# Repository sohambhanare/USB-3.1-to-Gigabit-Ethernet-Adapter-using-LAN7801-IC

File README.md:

# USB-3.1-to-Gigabit-Ethernet-Adapter-using-LAN7801-IC
KiCad design of a USB 3.1 Gen 1 to Gigabit Ethernet adapter based on the LAN7801 and KSZ9031RNX. Includes schematic, 4-layer impedance-controlled PCB layout, power supply design, simulations, and manufacturing Gerbers.

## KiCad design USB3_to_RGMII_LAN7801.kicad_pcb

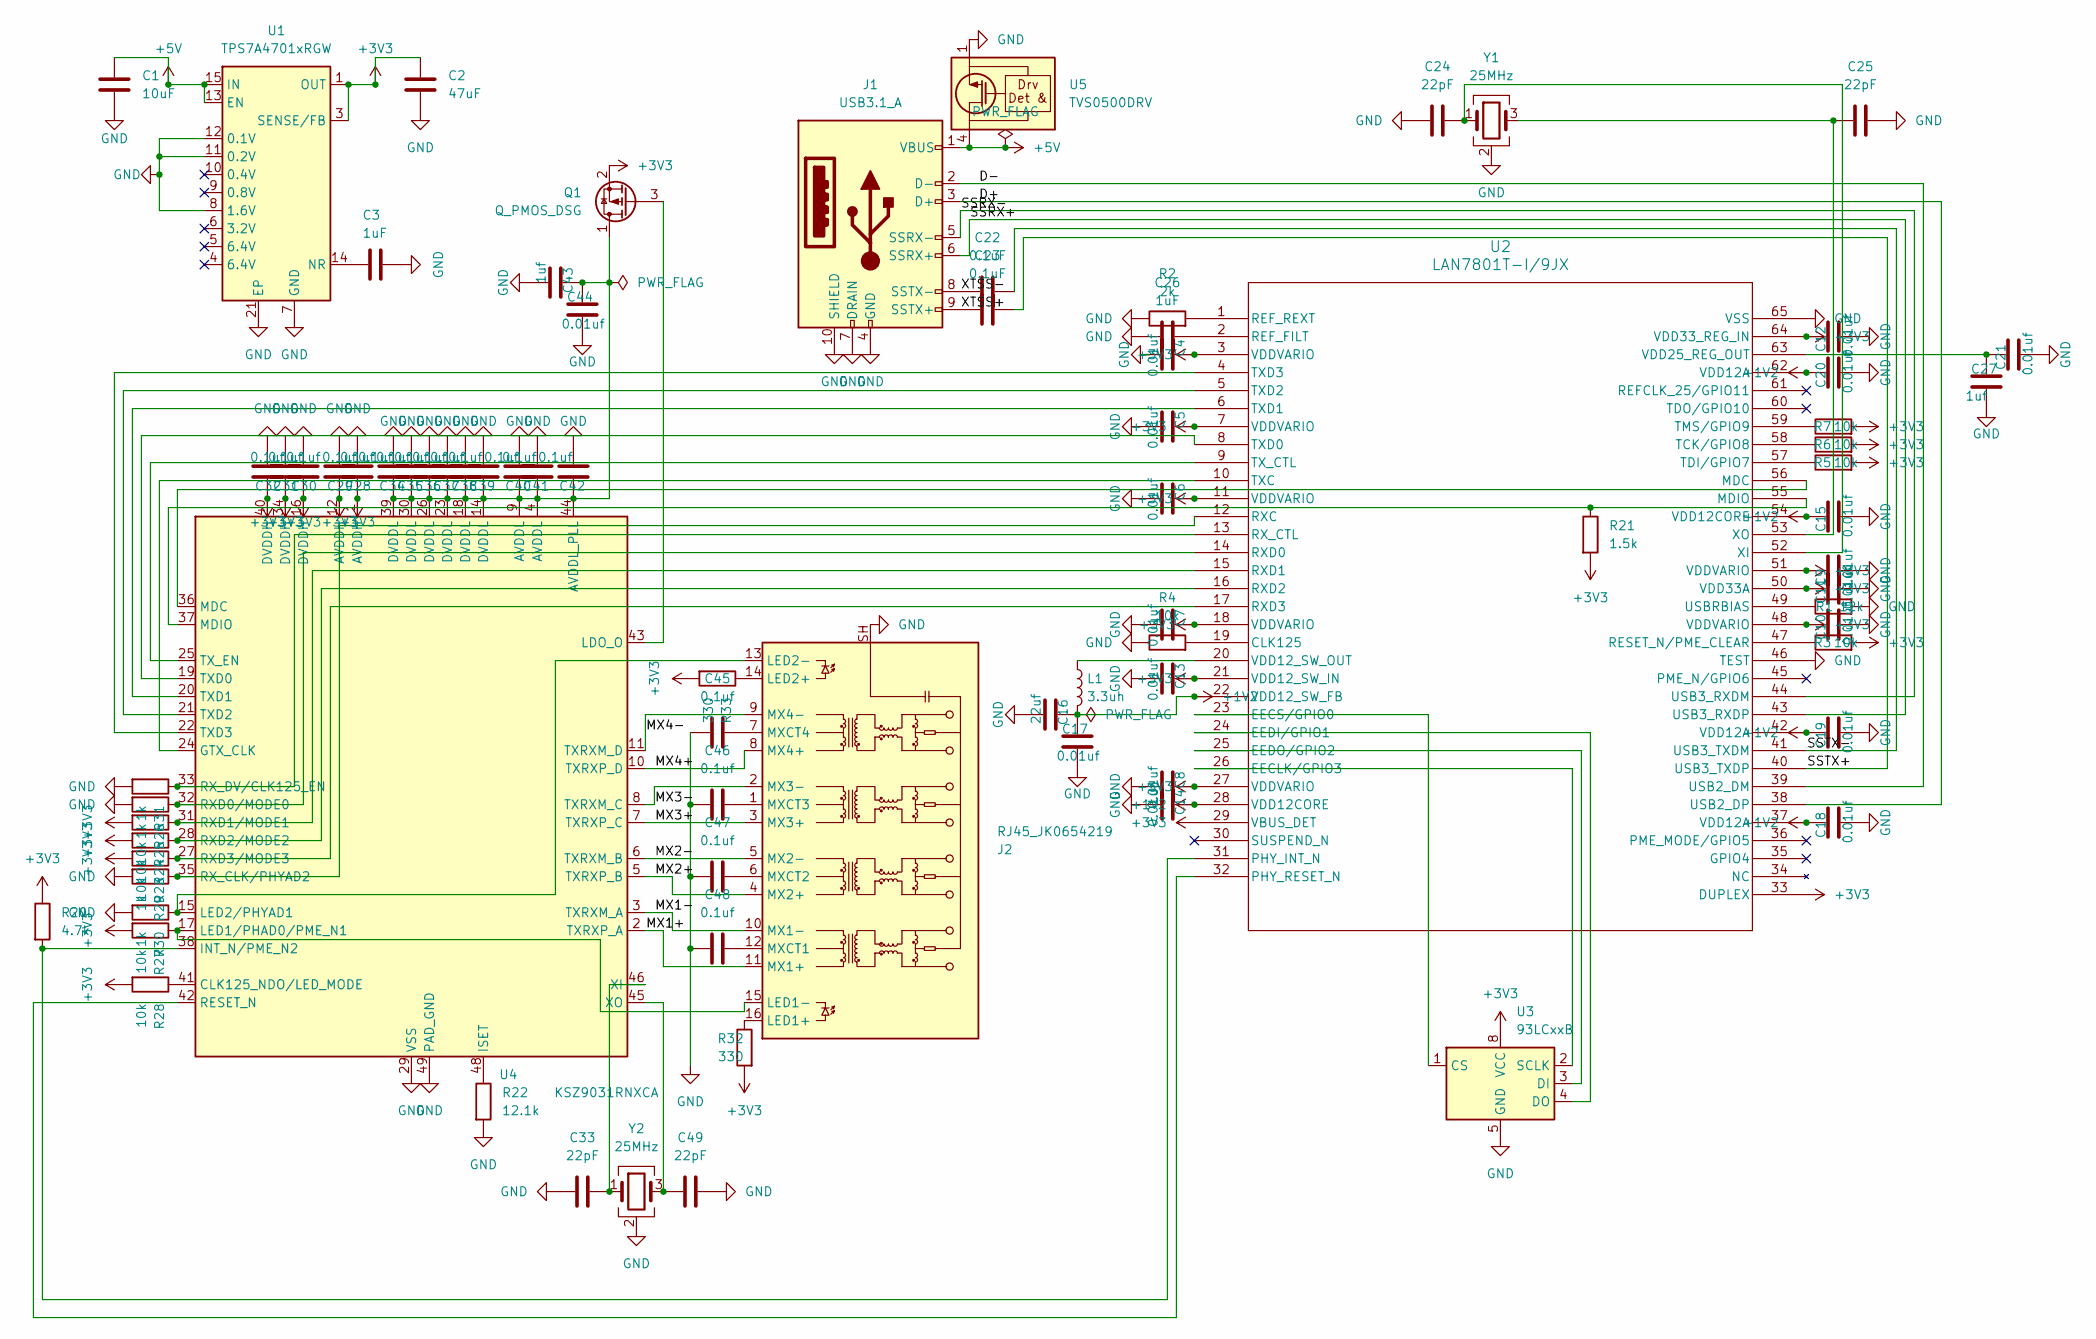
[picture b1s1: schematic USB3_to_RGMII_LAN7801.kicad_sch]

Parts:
C1: 10uF; C_0603_1608Metric
C2: 47uF; C_0603_1608Metric
C3, C26: 1uF; C_0603_1608Metric
C4, C5, C6, C7, C8, C9, C10, C11, C12, C13, C14, C15, C17, C18, C19, C20, C21, C44: 0.01uf; C_0603_1608Metric
C16: 22uf; C_0603_1608Metric
C22, C23: 0.1uF; C_0603_1608Metric
C24, C25, C33, C49: 22pF; C_0603_1608Metric
C27, C43: 1uf; C_0603_1608Metric
C28, C29, C30, C31, C32, C34, C35, C36, C37, C38, C39, C40, C41, C42, C45, C46, C47, C48: 0.1uf; C_0603_1608Metric
J1: USB3.1_A; USB3_A_Molex_48393-001
J2: RJ45_JK0654219; RJ45_Pulse_JK0654219NL_Horizontal
L1: 3.3uh; L_0603_1608Metric
Q1: Q_PMOS_DSG; SOT-23
R1: 12k; R_0603_1608Metric
R2: 2k; R_0603_1608Metric
R3, R4, R5, R6, R7, R23, R24, R25, R27, R28: 10k; R_0603_1608Metric
R20: 4.7k; R_0603_1608Metric
R21: 1.5k; R_0603_1608Metric
R22: 12.1k; R_0603_1608Metric
R26, R29, R30, R31: 1k; R_0603_1608Metric
R32, R33: 330; R_0603_1608Metric
U1: TPS7A4701xRGW; Texas_RGW0020A_VQFN-20-1EP_5x5mm_P0.65mm_EP3.15x3.15mm_Ther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
U2: LAN7801T-I/9JX; VQFN64_9X9X0P9_R4_MCH
U3: 93LCxxB; SOIC-8_3.9x4.9mm_P1.27mm
U4: KSZ9031RNXCA; QFN-48-1EP_7x7mm_P0.5mm_EP5.15x5.15mm
U5: TVS0500DRV; WSON-6-1EP_2x2mm_P0.65mm_EP1x1.6mm
Y1, Y2: 25MHz; Crystal_SMD_3225-4Pin_3.2x2.5mm

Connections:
+1V2: C14.1, C15.1, C16.1, C17.1, C18.1, C19.1, C20.1, L1.2, U2.22 (VDD12_SW_FB), U2.28 (VDD12CORE), U2.37 (VDD12A), U2.42 (VDD12A), U2.54 (VDD12CORE), U2.62 (VDD12A)
+3V3: C2.1, C4.1, C5.1, C6.1, C7.1, C8.1, C9.1, C10.1, C11.1, C12.1, C13.1, C28.1, C29.1, C30.1, C31.1, C32.1, Q1.2 (S), R3.2, R5.2, R6.2, R7.2, R20.1, R21.2, R23.2, R24.2, R25.2, R27.2, R28.2, R32.2, R33.2, U1.1 (OUT), U1.3 (SENSE/FB), U1.20 (OUT), U2.3 (VDDVARIO), U2.7 (VDDVARIO), U2.11 (VDDVARIO), U2.18 (VDDVARIO), U2.21 (VDD12_SW_IN), U2.27 (VDDVARIO), U2.29 (VBUS_DET), U2.33 (DUPLEX), U2.48 (VDDVARIO), U2.50 (VDD33A), U2.51 (VDDVARIO), U2.64 (VDD33_REG_IN), U3.8 (VCC), U4.1 (AVDDH), U4.12 (AVDDH), U4.16 (DVDDH), U4.34 (DVDDH), U4.40 (DVDDH)
+5V: C1.1, J1.1 (VBUS), U1.13 (EN), U1.15 (IN), U1.16 (IN), U5.4 (IN), U5.5 (IN), U5.6 (IN)
/D+: J1.3 (D+), U2.38 (USB2_DP)
/D-: J1.2 (D-), U2.39 (USB2_DM)
/MX1+: J2.11 (MX1+), U4.2 (TXRXP_A)
/MX1-: J2.10 (MX1-), U4.3 (TXRXM_A)
/MX2+: J2.4 (MX2+), U4.5 (TXRXP_B)
/MX2-: J2.5 (MX2-), U4.6 (TXRXM_B)
/MX3+: J2.3 (MX3+), U4.7 (TXRXP_C)
/MX3-: J2.2 (MX3-), U4.8 (TXRXM_C)
/MX4+: J2.8 (MX4+), U4.10 (TXRXP_D)
/MX4-: J2.9 (MX4-), U4.11 (TXRXM_D)
/SSRX+: J1.6 (SSRX+), U2.43 (USB3_RXDP)
/SSRX-: J1.5 (SSRX-), U2.44 (USB3_RXDM)
/SSTX+: C23.2, U2.40 (USB3_TXDP)
/SSTX-: C22.2, U2.41 (USB3_TXDM)
/XTSS+: C23.1, J1.9 (SSTX+)
/XTSS-: C22.1, J1.8 (SSTX-)
GND: C1.2, C2.2, C3.2, C4.2, C5.2, C6.2, C7.2, C8.2, C9.2, C10.2, C11.2, C12.2, C13.2, C14.2, C15.2, C16.2, C17.2, C18.2, C19.2, C20.2, C21.2, C24.1, C25.2, C26.1, C27.2, C28.2, C29.2, C30.2, C31.2, C32.2, C33.1, C34.2, C35.2, C36.2, C37.2, C38.2, C39.2, C40.2, C41.2, C42.2, C43.2, C44.2, C45.1, C46.1, C47.1, C48.1, C49.2, J1.4 (GND), J1.7 (DRAIN), J1.10 (SHIELD), J2.SH, R1.2, R2.1, R4.1, R22.2, R26.2, R29.2, R30.2, R31.2, U1.7 (GND), U1.8 (1.6V), U1.11 (0.2V), U1.12 (0.1V), U1.21 (EP), U2.46 (TEST), U2.65 (VSS), U3.5 (GND), U4.29 (VSS), U4.49 (PAD_GND), U5.1 (GND), U5.2 (GND), U5.3 (GND), U5.7 (GND), Y1.2 (G), Y1.4 (G), Y2.2 (G), Y2.4 (G)
unnamed: J2.16 (LED1+), R32.1
unnamed: J2.15 (LED1-), R27.1, U4.17 (LED1/PHAD0/PME_N1)
unnamed: J2.14 (LED2+), R33.1
unnamed: J2.13 (LED2-), R30.1, U4.15 (LED2/PHYAD1)
unnamed: C48.2, J2.12 (MXCT1)
unnamed: C47.2, J2.6 (MXCT2)
unnamed: C46.2, J2.1 (MXCT3)
unnamed: C45.2, J2.7 (MXCT4)
unnamed: C34.1, C35.1, C36.1, C37.1, C38.1, C39.1, C40.1, C41.1, C42.1, C43.1, C44.1, Q1.1 (D), U4.4 (AVDDL), U4.9 (AVDDL), U4.14 (DVDDL), U4.18 (DVDDL), U4.23 (DVDDL), U4.26 (DVDDL), U4.30 (DVDDL), U4.39 (DVDDL), U4.44 (AVDDL_PLL)
unnamed: Q1.3 (G), U4.43 (LDO_O)
unnamed: C3.1, U1.14 (NR)
unnamed: R4.2, U2.19 (CLK125)
unnamed: U2.26 (EECLK/GPIO3), U3.2 (SCLK)
unnamed: U2.23 (EECS/GPIO0), U3.1 (CS)
unnamed: U2.24 (EEDI/GPIO1), U3.4 (DO)
unnamed: U2.25 (EEDO/GPIO2), U3.3 (DI)
unnamed: U2.56 (MDC), U4.36 (MDC)
unnamed: R21.1, U2.55 (MDIO), U4.37 (MDIO)
unnamed: R20.2, U2.31 (PHY_INT_N), U4.38 (INT_N/PME_N2)
unnamed: U2.32 (PHY_RESET_N), U4.42 (RESET_N)
unnamed: C26.2, U2.2 (REF_FILT)
unnamed: R2.2, U2.1 (REF_REXT)
unnamed: R3.1, U2.47 (RESET_N/PME_CLEAR)
unnamed: R29.1, U2.12 (RXC), U4.35 (RX_CLK/PHYAD2)
unnamed: R26.1, U2.14 (RXD0), U4.32 (RXD0/MODE0)
unnamed: R25.1, U2.15 (RXD1), U4.31 (RXD1/MODE1)
unnamed: R24.1, U2.16 (RXD2), U4.28 (RXD2/MODE2)
unnamed: R23.1, U2.17 (RXD3), U4.27 (RXD3/MODE3)
unnamed: R31.1, U2.13 (RX_CTL), U4.33 (RX_DV/CLK125_EN)
unnamed: R6.1, U2.58 (TCK/GPIO8)
unnamed: R5.1, U2.57 (TDI/GPIO7)
unnamed: R7.1, U2.59 (TMS/GPIO9)
unnamed: U2.10 (TXC), U4.24 (GTX_CLK)
unnamed: U2.8 (TXD0), U4.19 (TXD0)
unnamed: U2.6 (TXD1), U4.20 (TXD1)
unnamed: U2.5 (TXD2), U4.21 (TXD2)
unnamed: U2.4 (TXD3), U4.22 (TXD3)
unnamed: U2.9 (TX_CTL), U4.25 (TX_EN)
unnamed: R1.1, U2.49 (USBRBIAS)
unnamed: L1.1, U2.20 (VDD12_SW_OUT)
unnamed: C21.1, C27.1, U2.63 (VDD25_REG_OUT)
unnamed: C24.2, U2.52 (XI), Y1.1
unnamed: C25.1, U2.53 (XO), Y1.3
unnamed: R28.1, U4.41 (CLK125_NDO/LED_MODE)
unnamed: R22.1, U4.48 (ISET)
unnamed: C33.2, U4.46 (XI), Y2.1
unnamed: C49.1, U4.45 (XO), Y2.3

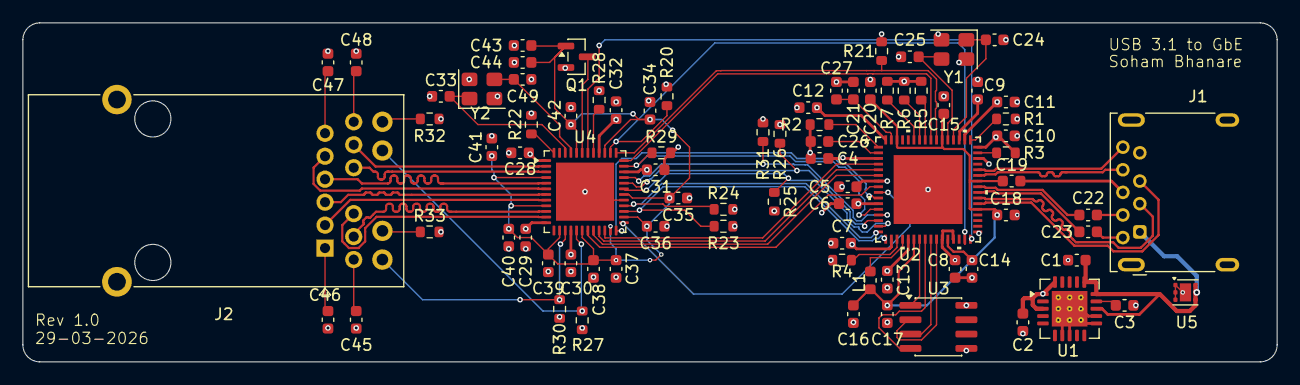
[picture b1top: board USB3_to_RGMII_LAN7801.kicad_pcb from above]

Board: 4 copper layers, 111.0 x 30.0 mm, 81 parts (0 on the bottom side), 67 nets.
